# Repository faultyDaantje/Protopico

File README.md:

# Protopico
A Microcontroller that is working on the RP2040 chip and is really easy for prototyping.

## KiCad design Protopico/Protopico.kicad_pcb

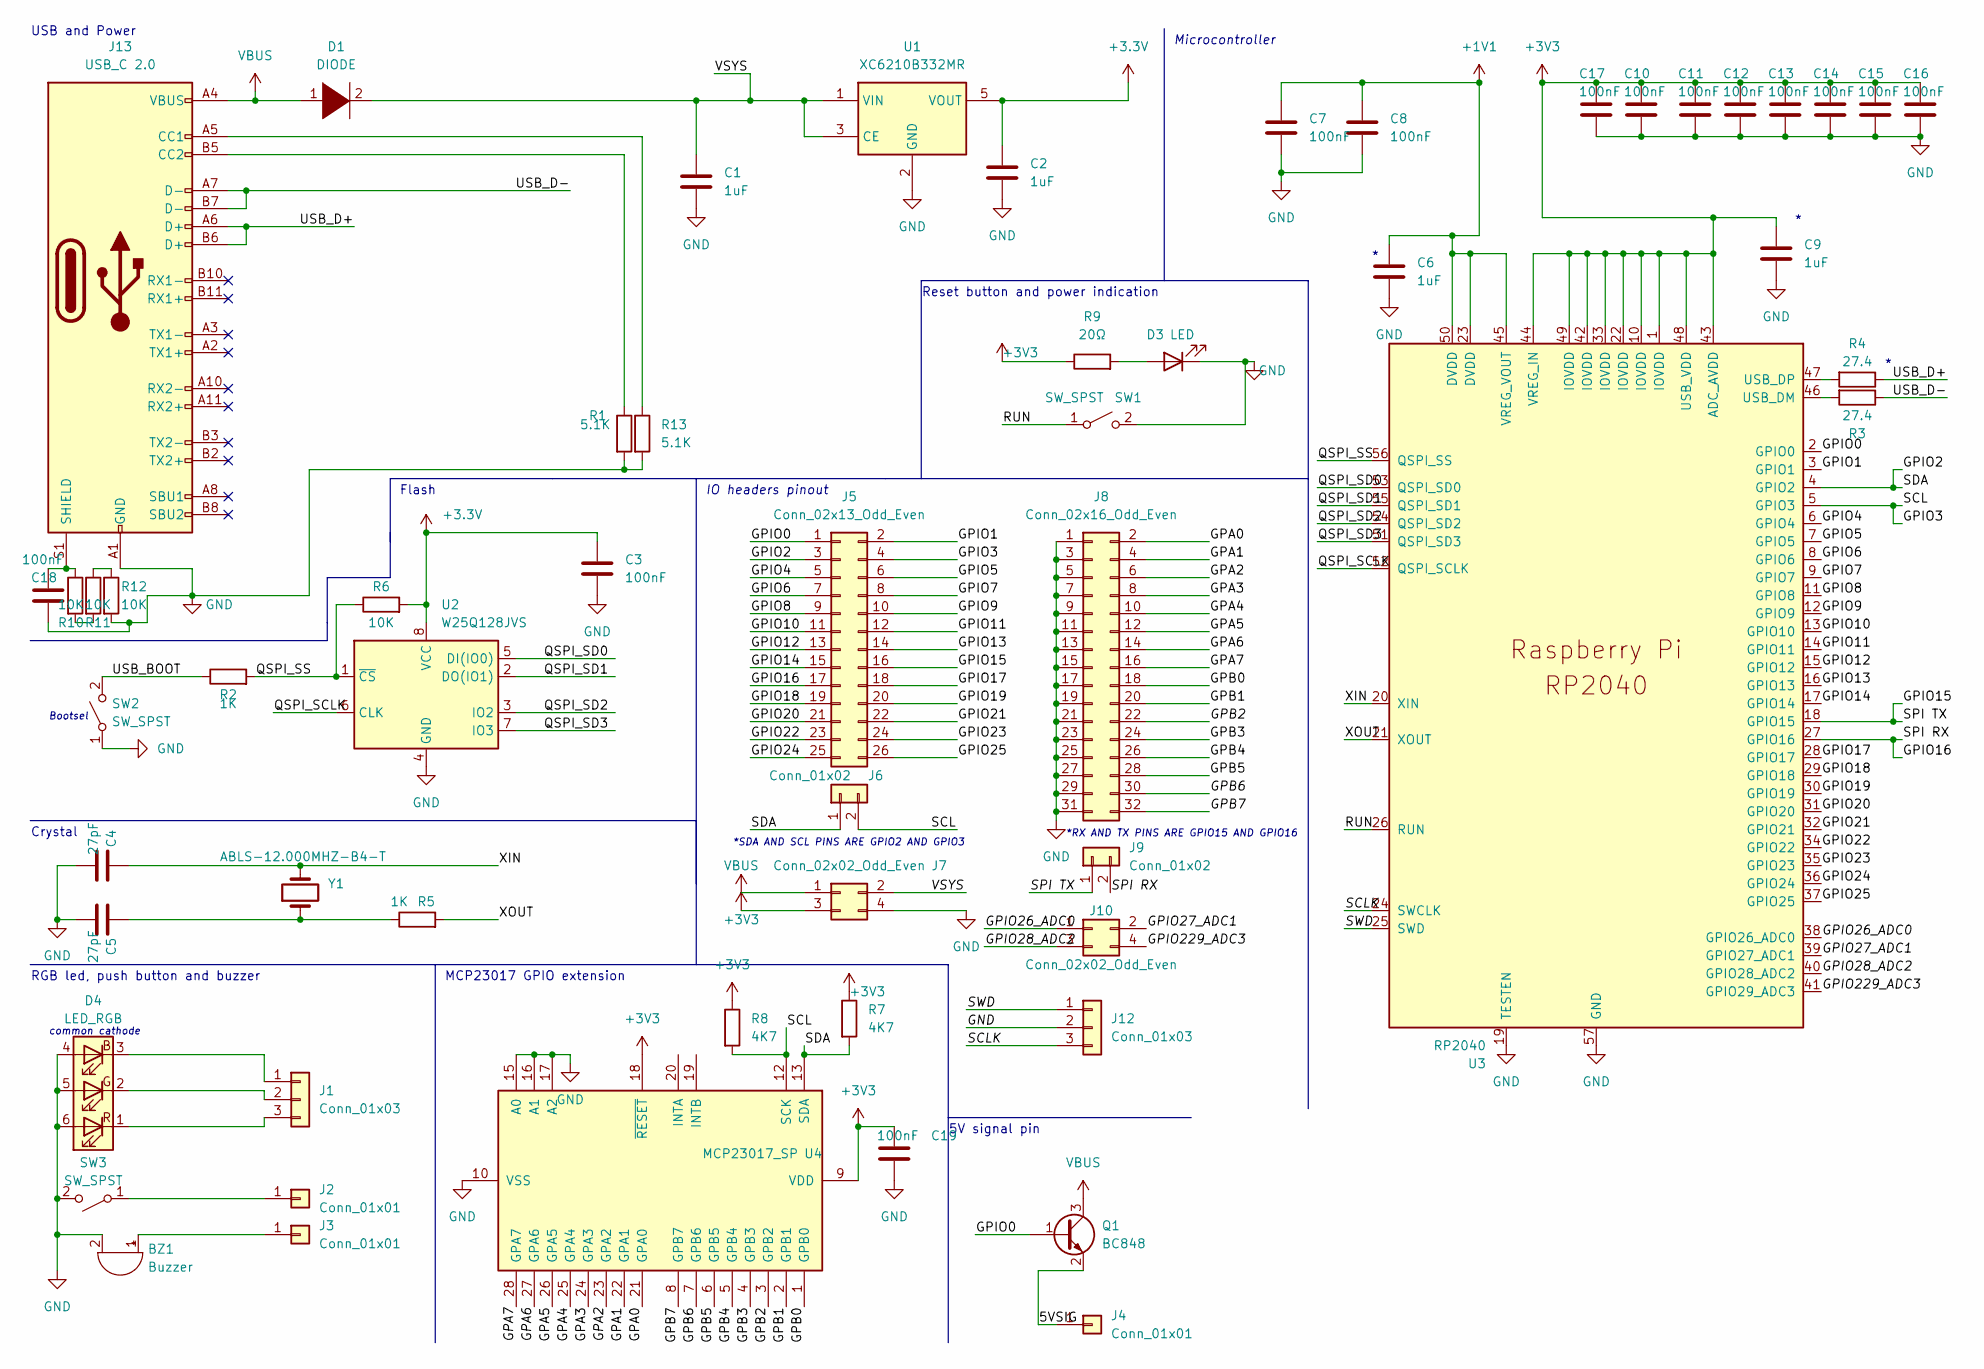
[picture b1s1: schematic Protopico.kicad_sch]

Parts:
BZ1: Buzzer; Buzzer_12x9.5RM7.6
C1, C2, C6, C9: 1uF; C_1206_3216Metric_Pad1.33x1.80mm_HandSolder
C3, C7, C8, C10, C11, C12, C13, C14, C15, C16, C17, C18, C19: 100nF; C_1206_3216Metric_Pad1.33x1.80mm_HandSolder
C4, C5: 27pF; C_1206_3216Metric_Pad1.33x1.80mm_HandSolder
D1: DIODE; D_1206_3216Metric_Pad1.42x1.75mm_HandSolder
D3: LED; LED_1206_3216Metric_Pad1.42x1.75mm_HandSolder
D4: LED_RGB; LED_D5.0mm-4_RGB
J1, J12: Conn_01x03; Pin_Header_Straight_1x03_Pitch2.54mm
J2, J3: Conn_01x01; Pin_Header_Straight_1x01_Pitch2.54mm
J4: Conn_01x01; Socket_Strip_Straight_1x01_Pitch2.54mm
J5: Conn_02x13_Odd_Even; Socket_Strip_Straight_2x13_Pitch2.54mm
J6: Conn_01x02; Socket_Strip_Straight_2x01_Pitch2.54mm
J7: Conn_02x02_Odd_Even; Pin_Header_Straight_2x02_Pitch2.54mm
J8: Conn_02x16_Odd_Even; Socket_Strip_Straight_2x16_Pitch2.54mm
J9: Conn_01x02; Socket_Strip_Straight_1x02_Pitch2.54mm
J10: Conn_02x02_Odd_Even; Socket_Strip_Straight_2x02_Pitch2.54mm
J13: USB_C 2.0; USB_C_Receptacle_GCT_USB4085
Q1: BC848; SOT-23
R1, R13: 5.1K; R_1206_3216Metric_Pad1.30x1.75mm_HandSolder
R2, R5: 1K; R_1206_3216Metric_Pad1.30x1.75mm_HandSolder
R3, R4: 27.4; R_1206_3216Metric_Pad1.30x1.75mm_HandSolder
R6, R10, R11, R12: 10K; R_1206_3216Metric_Pad1.30x1.75mm_HandSolder
R7, R8: 4K7; R_1206_3216Metric_Pad1.30x1.75mm_HandSolder
R9: 20Ω; R_1206_3216Metric_Pad1.30x1.75mm_HandSolder
SW1, SW2: SW_SPST; SW_Push_1P1T-SH_NO_CK_KMR2xxG
SW3: SW_SPST; SW_SPST_Omron_B3FS-105xP
U1: XC6210B332MR; SOT-23-5
U2: W25Q128JVS; SOIC-8_5.23x5.23mm_P1.27mm
U3: RP2040; RP2040-QFN-56
U4: MCP23017_SP; DIP-28_W7.62mm
Y1: ABLS-12.000MHZ-B4-T; ABLS7M2-16.000MHZ-D-2Y-T

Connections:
+1V1: C6.1, C7.1, C8.1, U3.23 (DVDD), U3.45 (VREG_VOUT), U3.50 (DVDD)
/5VSIG: J4.1, Q1.2 (E)
/GPA0: J8.2, U4.21 (GPA0)
/GPA1: J8.4, U4.22 (GPA1)
/GPA2: J8.6, U4.23 (GPA2)
/GPA3: J8.8, U4.24 (GPA3)
/GPA4: J8.10, U4.25 (GPA4)
/GPA5: J8.12, U4.26 (GPA5)
/GPA6: J8.14, U4.27 (GPA6)
/GPA7: J8.16, U4.28 (GPA7)
/GPB0: J8.18, U4.1 (GPB0)
/GPB1: J8.20, U4.2 (GPB1)
/GPB2: J8.22, U4.3 (GPB2)
/GPB3: J8.24, U4.4 (GPB3)
/GPB4: J8.26, U4.5 (GPB4)
/GPB5: J8.28, U4.6 (GPB5)
/GPB6: J8.30, U4.7 (GPB6)
/GPB7: J8.32, U4.8 (GPB7)
/GPIO0: J5.1, Q1.1 (B), U3.2 (GPIO0)
/GPIO1: J5.2, U3.3 (GPIO1)
/GPIO2: J5.3, J6.1, R7.2, U3.4 (GPIO2), U4.13 (SDA)
/GPIO3: J5.4, J6.2, R8.2, U3.5 (GPIO3), U4.12 (SCK)
/GPIO4: J5.5, U3.6 (GPIO4)
/GPIO5: J5.6, U3.7 (GPIO5)
/GPIO6: J5.7, U3.8 (GPIO6)
/GPIO7: J5.8, U3.9 (GPIO7)
/GPIO8: J5.9, U3.11 (GPIO8)
/GPIO9: J5.10, U3.12 (GPIO9)
/GPIO10: J5.11, U3.13 (GPIO10)
/GPIO11: J5.12, U3.14 (GPIO11)
/GPIO12: J5.13, U3.15 (GPIO12)
/GPIO13: J5.14, U3.16 (GPIO13)
/GPIO14: J5.15, U3.17 (GPIO14)
/GPIO15: J5.16, J9.1, U3.18 (GPIO15)
/GPIO16: J5.17, J9.2, U3.27 (GPIO16)
/GPIO17: J5.18, U3.28 (GPIO17)
/GPIO18: J5.19, U3.29 (GPIO18)
/GPIO19: J5.20, U3.30 (GPIO19)
/GPIO20: J5.21, U3.31 (GPIO20)
/GPIO21: J5.22, U3.32 (GPIO21)
/GPIO22: J5.23, U3.34 (GPIO22)
/GPIO23: J5.24, U3.35 (GPIO23)
/GPIO24: J5.25, U3.36 (GPIO24)
/GPIO25: J5.26, U3.37 (GPIO25)
/GPIO26_ADC0: J10.1, U3.38 (GPIO26_ADC0)
/GPIO27_ADC1: J10.2, U3.39 (GPIO27_ADC1)
/GPIO28_ADC2: J10.3, U3.40 (GPIO28_ADC2)
/GPIO229_ADC3: J10.4, U3.41 (GPIO29_ADC3)
/QSPI_SCLK: U2.6 (CLK), U3.52 (QSPI_SCLK)
/QSPI_SD0: U2.5 (DI(IO0)), U3.53 (QSPI_SD0)
/QSPI_SD1: U2.2 (DO(IO1)), U3.55 (QSPI_SD1)
/QSPI_SD2: U2.3 (IO2), U3.54 (QSPI_SD2)
/QSPI_SD3: U2.7 (IO3), U3.51 (QSPI_SD3)
/QSPI_SS: R2.2, R6.1, U2.1 (~CS), U3.56 (QSPI_SS)
/RUN: SW1.1 (A), U3.26 (RUN)
/SCLK: J12.3, U3.24 (SWCLK)
/SWD: J12.1, U3.25 (SWD)
/USB_BOOT: R2.1, SW2.2 (B)
/USB_D+: J13.A6 (D+), J13.B6 (D+), R4.1
/USB_D-: J13.A7 (D-), J13.B7 (D-), R3.1
/VSYS: C1.1, D1.2 (A), J7.2, U1.1 (VIN), U1.3 (CE)
/XIN: C4.1, U3.20 (XIN), Y1.2
/XOUT: R5.2, U3.21 (XOUT)
GND: BZ1.2 (+), C1.2, C2.2, C3.2, C4.2, C5.2, C6.2, C7.2, C8.2, C9.2, C10.2, C11.2, C12.2, C13.2, C14.2, C15.2, C16.2, C17.2, C18.2, C19.2, D3.1 (K), D4.4 (BA), D4.5 (GA), D4.6 (RA), J7.4, J8.1, J8.3, J8.5, J8.7, J8.9, J8.11, J8.13, J8.15, J8.17, J8.19, J8.21, J8.23, J8.25, J8.27, J8.29, J8.31, J12.2, J13.A1 (GND), J13.A12 (GND), J13.B1 (GND), J13.B12 (GND), R1.2, R12.2, R13.2, SW1.2 (B), SW2.1 (A), SW3.2 (B), U1.2 (GND), U2.4 (GND), U3.19 (TESTEN), U3.57 (GND), U4.10 (VSS), U4.15 (A0), U4.16 (A1), U4.17 (A2)
unnamed: BZ1.1 (-), J3.1
unnamed: C5.1, R5.1, Y1.1
unnamed: C18.1, J13.S1 (SHIELD), R10.1
unnamed: D3.2 (A), R9.2
unnamed: D4.1 (RK), J1.3
unnamed: D4.2 (GK), J1.2
unnamed: D4.3 (BK), J1.1
unnamed: J2.1, SW3.1 (A)
unnamed: J13.A5 (CC1), R13.1
unnamed: J13.B5 (CC2), R1.1
unnamed: R3.2, U3.46 (USB_DM)
unnamed: R4.2, U3.47 (USB_DP)
unnamed: R10.2, R11.2
unnamed: R11.1, R12.1
VBUS: D1.1 (K), J7.1, J13.A4 (VBUS), J13.A9 (VBUS), J13.B4 (VBUS), J13.B9 (VBUS), Q1.3 (C)

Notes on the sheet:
Bootsel
Flash
MCP23017 GPIO extension
5V signal pin
common cathode
*RX AND TX PINS ARE GPIO15 AND GPIO16
*SDA AND SCL PINS ARE GPIO2 AND GPIO3
Reset button and power indication
RGB led, push button and buzzer
Crystal
Microcontroller
USB and Power
IO headers pinout

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
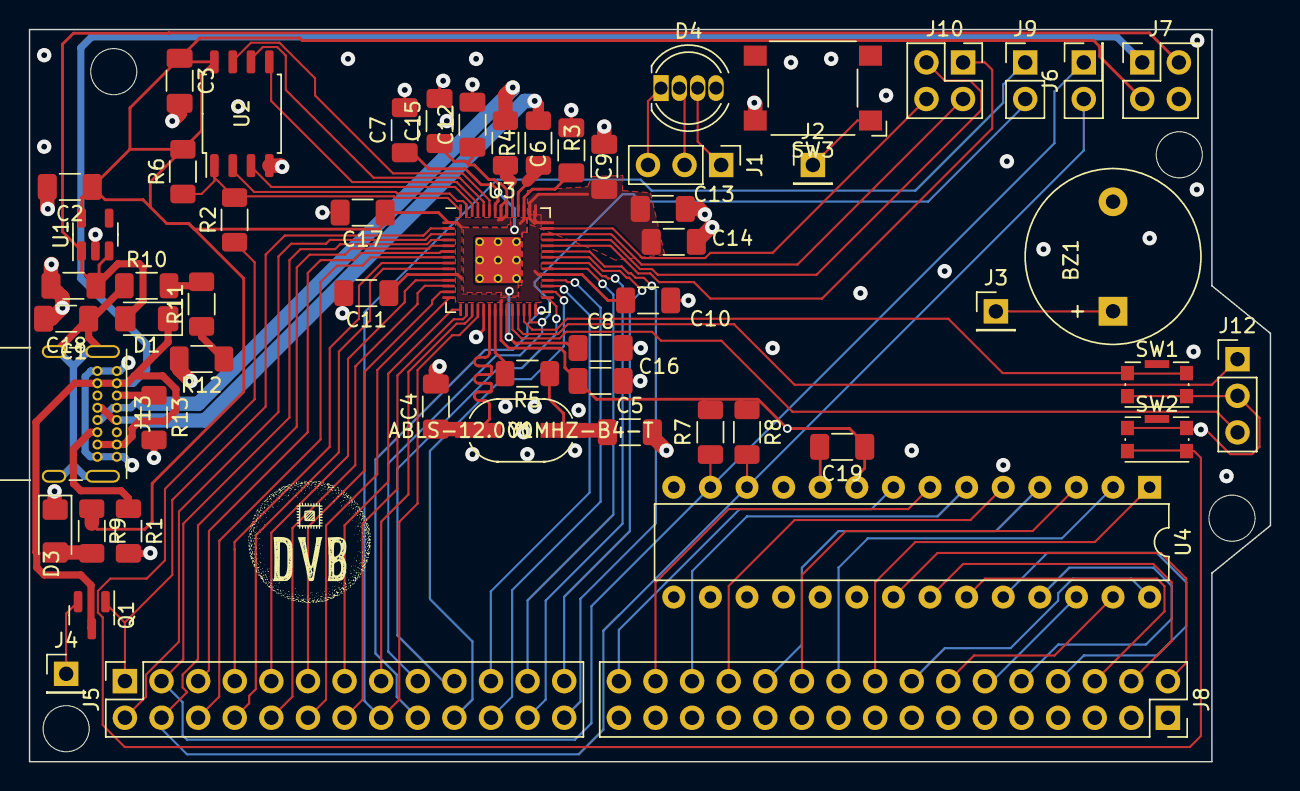
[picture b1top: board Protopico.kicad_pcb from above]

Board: 4 copper layers, 86.1 x 50.8 mm, 57 parts (0 on the bottom side), 80 nets.

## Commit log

2022-06-27 added LICENSE and README.md
2022-06-27 added images of the board
2022-06-28 improved pcb and schematic
2022-06-29 improved pcb
2022-06-29 added logo to pcb

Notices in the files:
parts and their libraries:
Copyright 2021 Accelerated Designs. All rights reserved.
